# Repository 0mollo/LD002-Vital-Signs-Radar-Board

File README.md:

# LD6002 Vital Signs Radar PCB

## 📘 Overview
The **LD6002 Vital Signs Radar PCB** is an open-source hardware design that uses the **Hi-Link LD6002 60 GHz radar sensor** for non-contact detection of **human presence, motion, respiration, and heart rate**.  
The board is designed in **KiCad** and integrates seamlessly with the **ESP32-C3 Mini** microcontroller for data acquisition and wireless communication.

## ⚙️ Features
- High-precision **60 GHz FMCW radar** sensing
- Detection of **breathing and heart rate** through low-power Doppler processing
- Compact **piggyback form factor** for embedded applications
- Designed for **ESP32-C3 Mini** integration
- Fully open-source design files under **CERN-OHL-P v2**

## 🔧 Technical Description
The design is based on the **Hi-Link LD6002** module, which provides motion and vital sign information using advanced radar algorithms.  
The PCB hosts the LD6002 sensor module and routing interface to the ESP32-C3 Mini through standard pin headers.

The system can be integrated into smart IoT devices such as:
- Smart home automation (presence sensing)
- Health monitoring stations
- Human–machine interaction systems
- Industrial safety monitoring

## 🧾 Bill of Materials (BOM)
A detailed list of all components is included in the **Bill of Materials** file:  
📄 [Bom File.xlsx](Bom%20File.xlsx)

## 🧠 Usage and Integration Notes
1. Power the module with **3.3 V DC** regulated supply.  
2. Connect serial data pins (TX/RX) to the **ESP32-C3 Mini UART** interface.  
3. Configure the MCU firmware to interpret radar serial output for presence and vital sign data.  
4. For optimal performance, ensure there are no metallic obstructions in the sensing path.  

## 🧩 Hardware Design
All design files were created using **KiCad**.  
To open the project:
1. Clone or download this repository.
2. Open `project.kicad_pro` in KiCad 7.0 or later.

## 📜 License
This project is licensed under the **CERN Open Hardware Licence v2 – Permissive (CERN-OHL-P v2)**.  
You are free to use, modify, and distribute this design, provided that proper attribution is maintained.  
See the [LICENSE](LICENSE) file for details.

## 👤 Author Information
**Author:** [Brian Omollo](https://www.linkedin.com/in/brian-omollo-25a71620b/)  
**Organization:** Carenuity  
**License:** CERN-OHL-P v2 (Permissive)  
**Design Tool:** KiCad  

## 📖 Citation

If you use this design in your work, please cite it as follows:

> Omollo, B. (2025). *LD6002 Vital Signs Radar PCB (v1.0)*. Carenuity Open Hardware Project. Licensed under CERN-OHL-P v2.

**BibTeX:**
```bibtex
@hardware{omollo2025ld6002,
  author    = {Brian Omollo},
  title     = {LD6002 Vital Signs Radar PCB (v1.0)},
  year      = {2025},
  publisher = {Carenuty Open Hardware Project},
  license   = {CERN-OHL-P v2},
  url       = {https://github.com/Carenuity/LD6002-Vital-Signs-Radar-PCB}
}

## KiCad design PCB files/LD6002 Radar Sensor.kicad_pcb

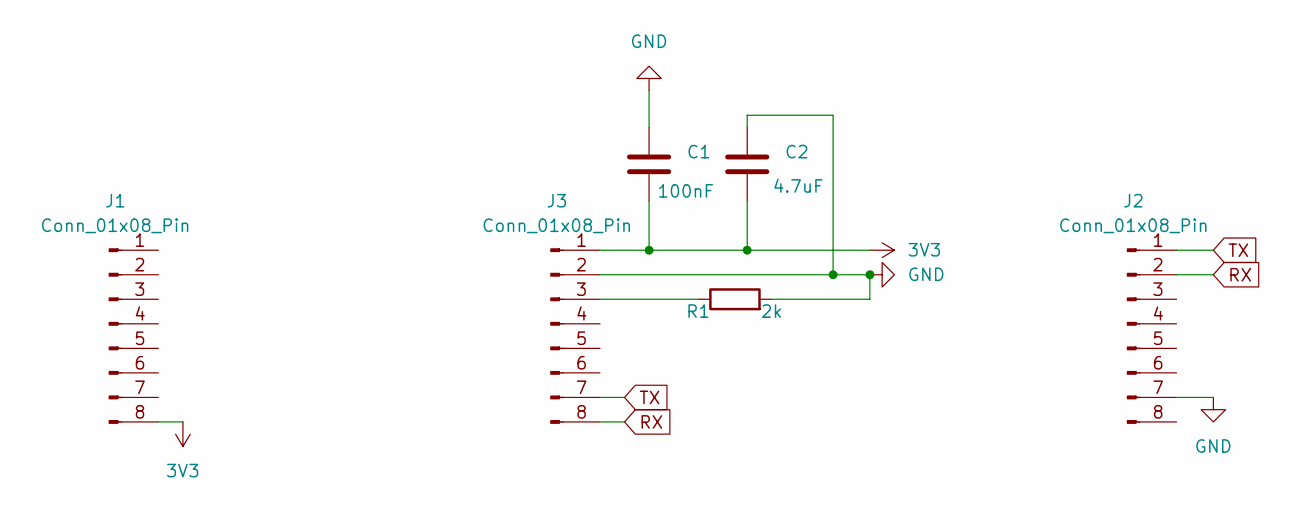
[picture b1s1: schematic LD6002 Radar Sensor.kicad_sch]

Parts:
C1: 100nF; C_0603_1608Metric
C2: 4.7uF; C_0603_1608Metric
J1, J2: Conn_01x08_Pin; PinHeader_1x08_P2.54mm_Vertical
J3: Conn_01x08_Pin; PinHeader_1x08_P2.00mm_Vertical
R1: 2k; R_0603_1608Metric

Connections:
3V3: C1.2, C2.2, J1.8, J3.1
GND: C1.1, C2.1, J2.7, J3.2, R1.2
unnamed: J3.3, R1.1
RX: J2.2, J3.8
TX: J2.1, J3.7

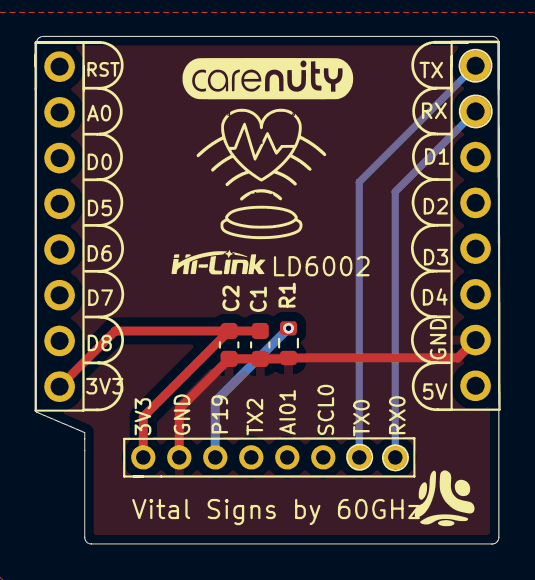
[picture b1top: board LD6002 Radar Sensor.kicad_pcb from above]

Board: 2 copper layers, 25.7 x 28.2 mm, 6 parts (0 on the bottom side), 5 nets.

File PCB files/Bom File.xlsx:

Designator | Footprint | Quantity | Value | LCSC Part #
C1 | 603 | 1 | 100nF | C14663
C2 | 603 | 1 | 4.7uF | C48579268
R1 | 603 | 1 | 2k | C2907137

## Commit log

2025-10-19 Create LICENSE
2025-10-20 Update LICENSE
2025-10-20 Create Project.Kicad_pro (placeholder)
2025-10-20 Create Top view
